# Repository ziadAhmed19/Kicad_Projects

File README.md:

## PCB Design Portfolio

This repository contains a collection of PCB design projects created using KiCad. Each project includes an interactive PCB viewer (iBOM), PCB images, and design files.

### Portfolio Website

https://ziadahmed19.github.io/Kicad_Projects/

### Featured Projects

- Tiny Boost Converter
- Breadboard Power Supply
- 2-Layer MCU Datalogger
- 4-Layer MCU Datalogger

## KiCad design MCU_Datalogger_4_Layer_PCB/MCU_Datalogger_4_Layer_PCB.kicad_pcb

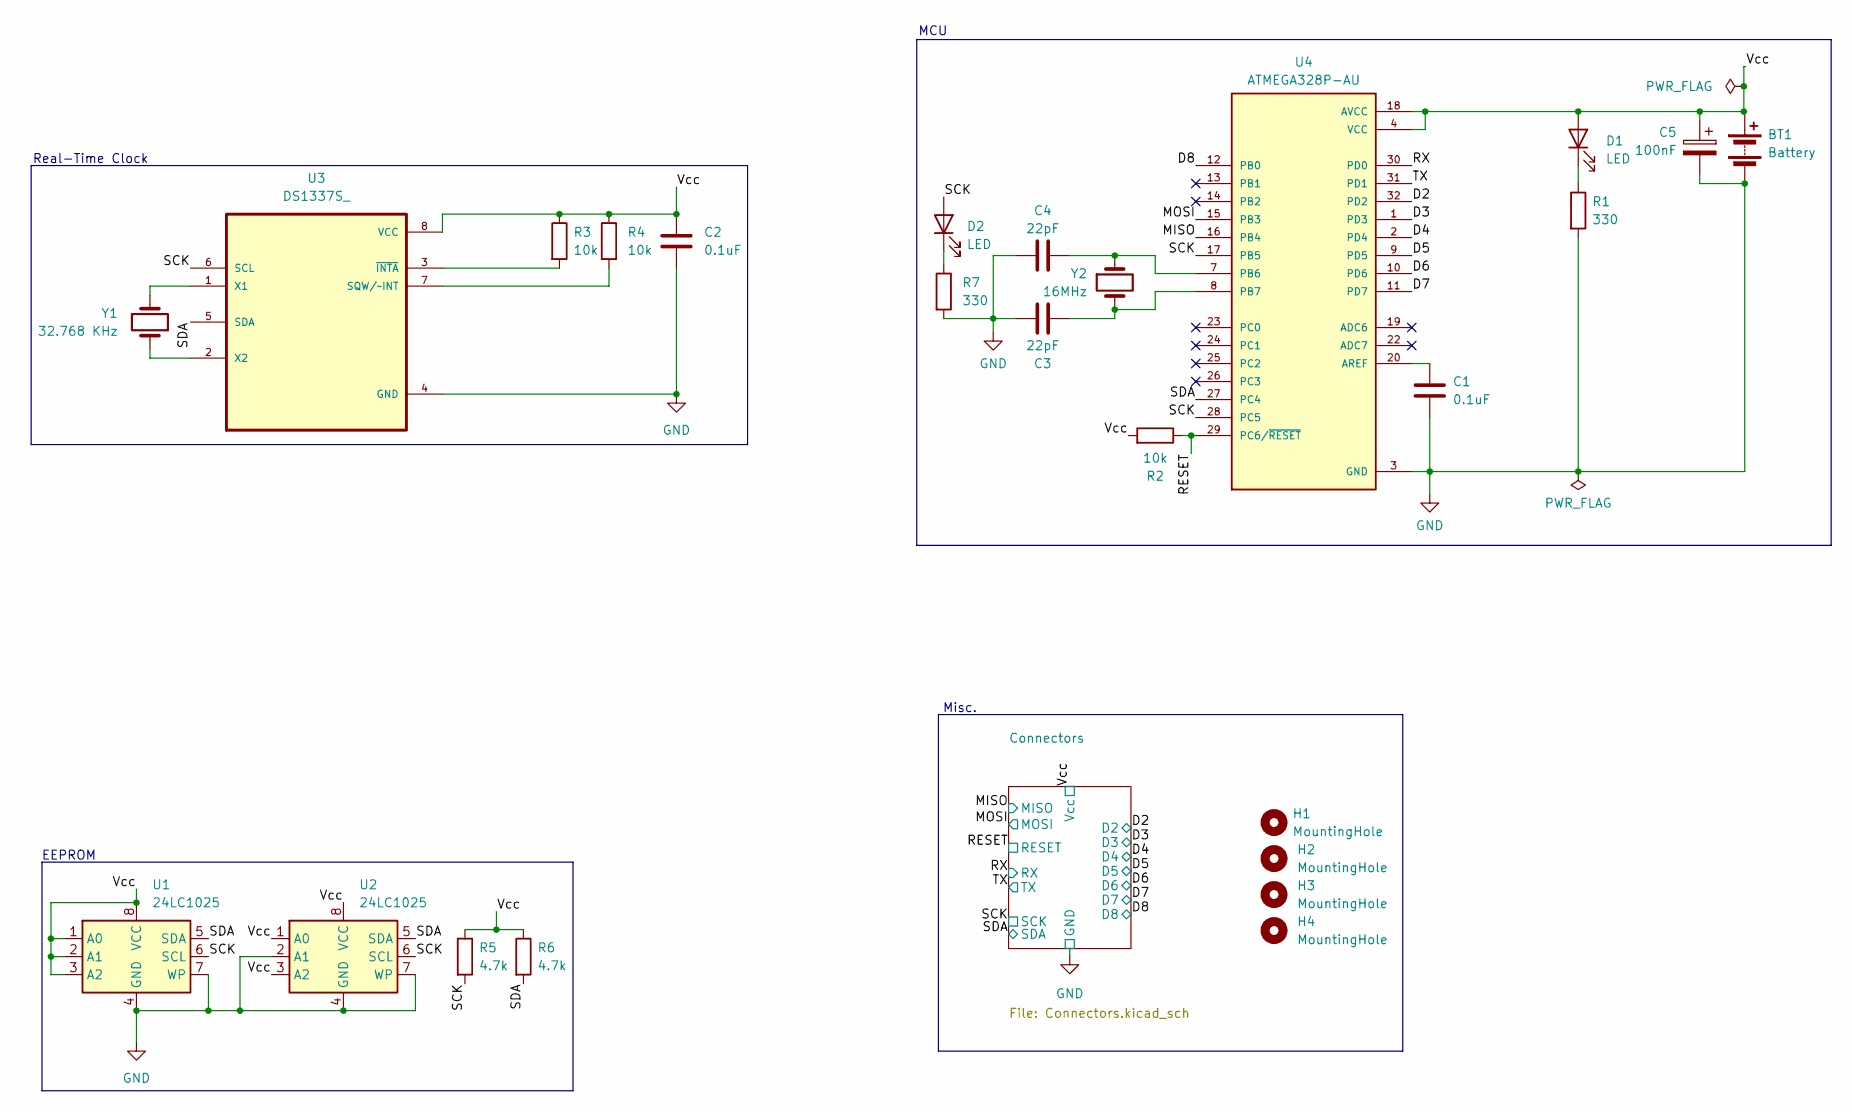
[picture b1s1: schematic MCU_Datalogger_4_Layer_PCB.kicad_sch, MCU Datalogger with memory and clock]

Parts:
BT1: Battery; PinHeader_1x02_P2.54mm_Vertical
C1, C2: 0.1uF; C_0805_2012Metric
C3, C4: 22pF; C_0805_2012Metric
C5: 100nF; C_0805_2012Metric
D1, D2: LED; LED_0805_2012Metric
H1, H2, H3, H4: MountingHole; MountingHole_2.1mm
R1, R7: 330; R_0805_2012Metric
R2, R3, R4: 10k; R_0805_2012Metric
R5, R6: 4.7k; R_0805_2012Metric
U1, U2: 24LC1025; SOIC-8_3.9x4.9mm_P1.27mm
U3: DS1337S_; SOIC127P600X175-8N
U4: ATMEGA328P-AU; QFP80P900X900X120-32N; PARTREV 8271A
Y1: 32.768 KHz; Crystal_SMD_5032-2Pin_5.0x3.2mm
Y2: 16MHz; Crystal_SMD_5032-2Pin_5.0x3.2mm

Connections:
/D2: U4.32 (PD2); also elsewhere on the board
/D3: U4.1 (PD3); also elsewhere on the board
/D4: U4.2 (PD4); also elsewhere on the board
/D5: U4.9 (PD5); also elsewhere on the board
/D6: U4.10 (PD6); also elsewhere on the board
/D7: U4.11 (PD7); also elsewhere on the board
/D8: U4.12 (PB0); also elsewhere on the board
/MISO: U4.16 (PB4); also elsewhere on the board
/MOSI: U4.15 (PB3); also elsewhere on the board
/RESET: R2.1, U4.29 (PC6/~RESET); also elsewhere on the board
/RX: U4.30 (PD0); also elsewhere on the board
/SCK: D2.2 (A), R5.2, U1.6 (SCL), U2.6 (SCL), U3.6 (SCL), U4.17 (PB5), U4.28 (PC5); also elsewhere on the board
/SDA: R6.2, U1.5 (SDA), U2.5 (SDA), U3.5 (SDA), U4.27 (PC4); also elsewhere on the board
/TX: U4.31 (PD1); also elsewhere on the board
GND: BT1.2 (-), C1.2, C2.2, C3.1, C4.2, C5.2, R1.2, R7.2, U1.4 (GND), U1.7 (WP), U2.2 (A1), U2.4 (GND), U2.7 (WP), U3.4 (GND), U4.3 (GND), U4.5 (GND), U4.21 (GND); also elsewhere on the board
unnamed: D1.1 (K), R1.1
unnamed: D2.1 (K), R7.1
unnamed: R4.2, U3.7 (SQW/~INT)
unnamed: U3.1 (X1), Y1.2
unnamed: U3.2 (X2), Y1.1
unnamed: R3.2, U3.3 (~INTA)
unnamed: C1.1, U4.20 (AREF)
unnamed: C4.1, U4.7 (PB6), Y2.1
unnamed: C3.2, U4.8 (PB7), Y2.2
VCC: BT1.1 (+), C2.1, C5.1, D1.2 (A), R2.2, R3.1, R4.1, R5.1, R6.1, U1.1 (A0), U1.2 (A1), U1.3 (A2), U1.8 (VCC), U2.1 (A0), U2.3 (A2), U2.8 (VCC), U3.8 (VCC), U4.4 (VCC), U4.6 (VCC), U4.18 (AVCC); also elsewhere on the board

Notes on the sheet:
MCU
EEPROM
Real-Time Clock
Misc.

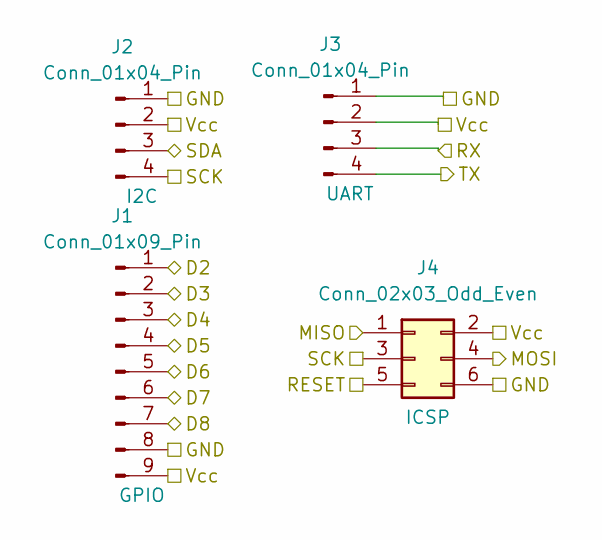
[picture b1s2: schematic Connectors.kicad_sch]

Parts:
J1: Conn_01x09_Pin; PinHeader_1x09_P2.54mm_Vertical
J2, J3: Conn_01x04_Pin; PinHeader_1x04_P2.54mm_Vertical
J4: Conn_02x03_Odd_Even; PinHeader_2x03_P2.54mm_Vertical

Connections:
/D2: J1.1; also elsewhere on the board
/D3: J1.2; also elsewhere on the board
/D4: J1.3; also elsewhere on the board
/D5: J1.4; also elsewhere on the board
/D6: J1.5; also elsewhere on the board
/D7: J1.6; also elsewhere on the board
/D8: J1.7; also elsewhere on the board
/MISO: J4.1; also elsewhere on the board
/MOSI: J4.4; also elsewhere on the board
/RESET: J4.5; also elsewhere on the board
/RX: J3.3; also elsewhere on the board
/SCK: J2.4, J4.3; also elsewhere on the board
/SDA: J2.3; also elsewhere on the board
/TX: J3.4; also elsewhere on the board
GND: J1.8, J2.1, J3.1, J4.6; also elsewhere on the board
VCC: J1.9, J2.2, J3.2, J4.2; also elsewhere on the board

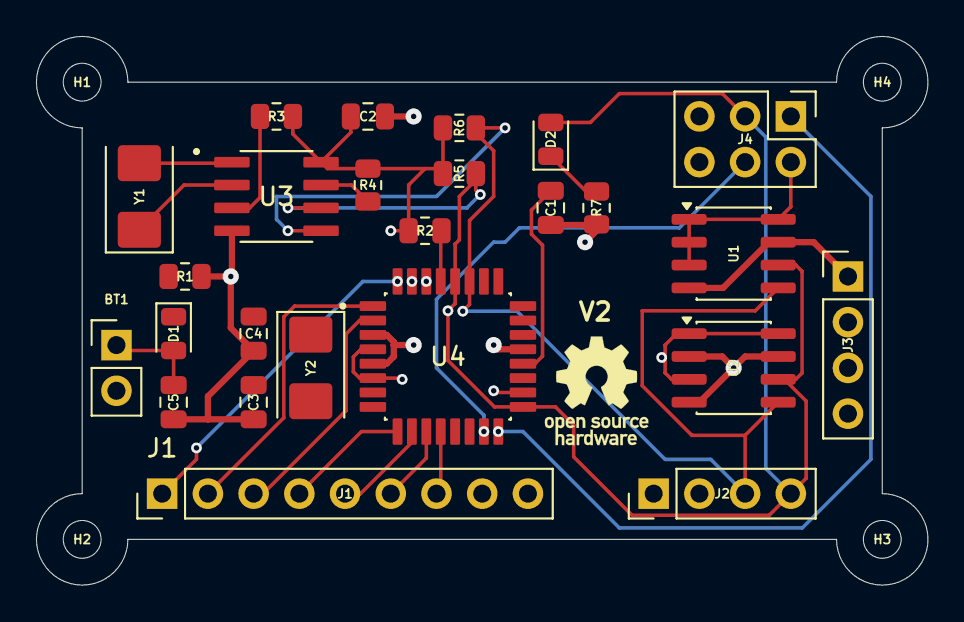
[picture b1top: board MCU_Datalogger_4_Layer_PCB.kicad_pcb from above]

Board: 4 copper layers, 49.5 x 30.5 mm, 29 parts (0 on the bottom side), 25 nets.

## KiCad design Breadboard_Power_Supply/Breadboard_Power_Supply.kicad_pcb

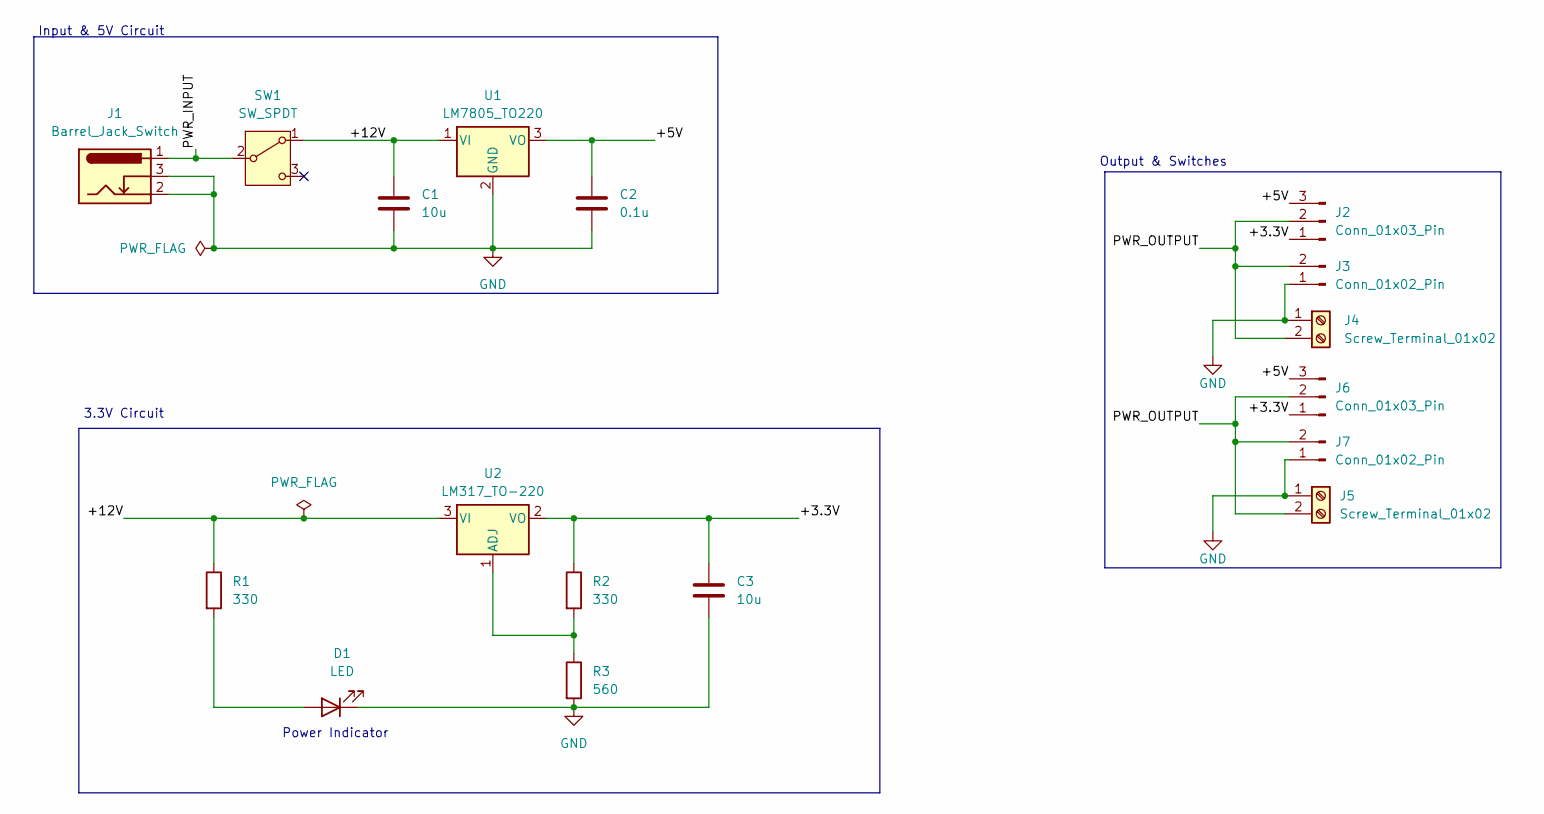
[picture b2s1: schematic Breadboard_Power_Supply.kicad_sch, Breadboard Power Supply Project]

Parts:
C1, C3: 10u; C_Disc_D3.0mm_W1.6mm_P2.50mm
C2: 0.1u; C_Disc_D3.0mm_W1.6mm_P2.50mm
D1: LED; LED_D5.0mm
J1: Barrel_Jack_Switch; BarrelJack_Horizontal
J2, J6: Conn_01x03_Pin; PinHeader_1x03_P2.54mm_Vertical
J3, J7: Conn_01x02_Pin; PinHeader_1x02_P2.54mm_Vertical
J4, J5: Screw_Terminal_01x02; TerminalBlock_MaiXu_MX126-5.0-02P_1x02_P5.00mm
R1, R2: 330; R_Axial_DIN0207_L6.3mm_D2.5mm_P7.62mm_Horizontal
R3: 560; R_Axial_DIN0207_L6.3mm_D2.5mm_P7.62mm_Horizontal
SW1: SW_SPDT; SW_Slide-03_Wuerth-WS-SLTV_10x2.5x6.4_P2.54mm
U1: LM7805_TO220; TO-220-3_Vertical
U2: LM317_TO-220; TO-220-3_Vertical

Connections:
/+3.3V: C3.1, J2.1, J6.1, R2.1, U2.2 (VO)
/+5V: C2.1, J2.3, J6.3, U1.3 (VO)
/+12V: C1.1, R1.1, SW1.1 (A), U1.1 (VI), U2.3 (VI)
/PWR_INPUT: J1.1, SW1.2 (B)
/PWR_OUTPUT: J2.2, J3.2, J4.2, J5.2, J6.2, J7.2
GND: C1.2, C2.2, C3.2, D1.1 (K), J1.2, J1.3, J3.1, J4.1, J5.1, J7.1, R3.2, U1.2 (GND)
unnamed: D1.2 (A), R1.2
unnamed: R2.2, R3.1, U2.1 (ADJ)

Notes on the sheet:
3.3V Circuit
Power Indicator
Output & Switches
Input & 5V Circuit

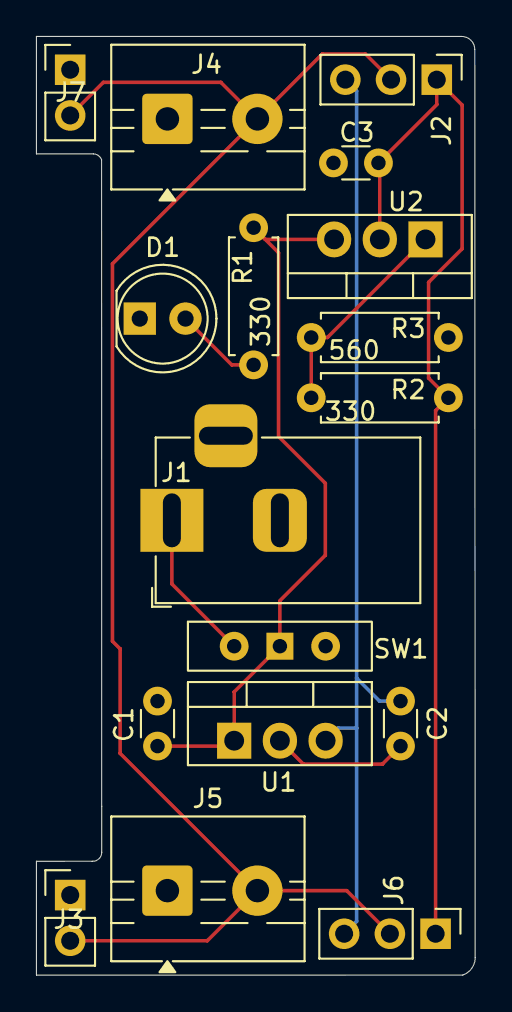
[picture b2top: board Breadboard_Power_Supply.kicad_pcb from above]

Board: 2 copper layers, 24.4 x 52.1 mm, 17 parts (0 on the bottom side), 8 nets.

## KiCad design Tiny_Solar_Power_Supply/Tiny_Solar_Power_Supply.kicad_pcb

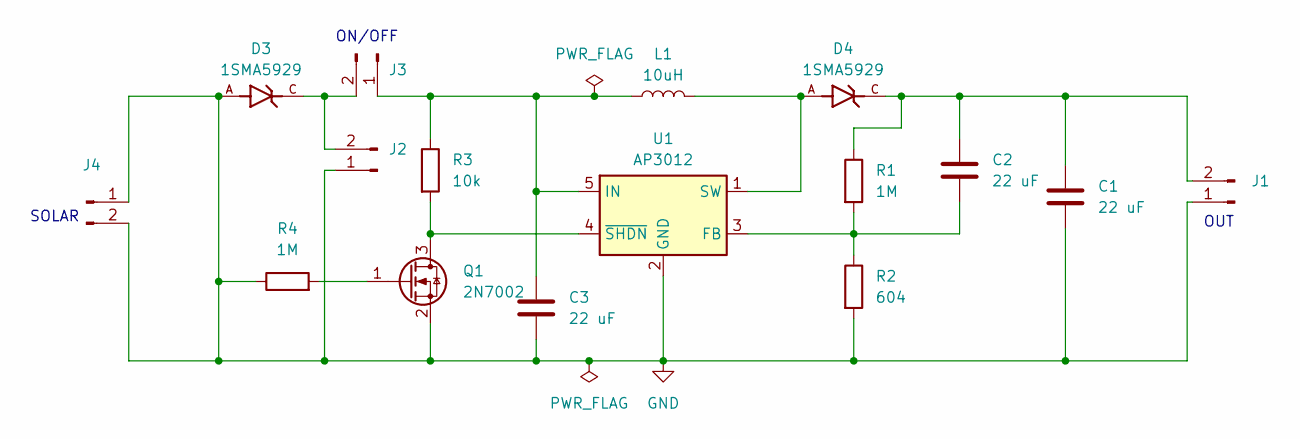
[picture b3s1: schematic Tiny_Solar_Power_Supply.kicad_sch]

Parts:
C1: 22 uF; C_0805_2012Metric
C2, C3: 22 uF; C_1206_3216Metric
D3, D4: 1SMA5929; DIOM4325X250N; PARTREV B2102; DigiKey_Part_Number 1801-1SMA5929CT-ND
J1, J2, J3: Conn_01x02_Pin; PinHeader_1x02_P2.00mm_Vertical
J4: Conn_01x02_Pin; TE_440055-2_1x02_P2.00mm_Horizontal
L1: 10uH; L_1210_3225Metric
Q1: 2N7002; SOT-23
R1, R4: 1M; R_0805_2012Metric
R2: 604; R_0805_2012Metric
R3: 10k; R_0805_2012Metric
U1: AP3012; SOT-23-5

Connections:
GND: C1.2, C3.2, D3.A, J1.1, J2.1, J4.1, J4.2, Q1.2 (S), R2.2, R4.1, U1.2 (GND)
unnamed: C1.1, C2.1, D4.C, J1.2, R1.1
unnamed: D3.C, J2.2, J3.2
unnamed: C3.1, J3.1, L1.1, R3.1, U1.5 (IN)
unnamed: Q1.3 (D), R3.2, U1.4 (~SHDN)
unnamed: Q1.1 (G), R4.2
unnamed: C2.2, R1.2, R2.1, U1.3 (FB)
unnamed: D4.A, L1.2, U1.1 (SW)

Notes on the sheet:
OUT
ON/OFF
SOLAR

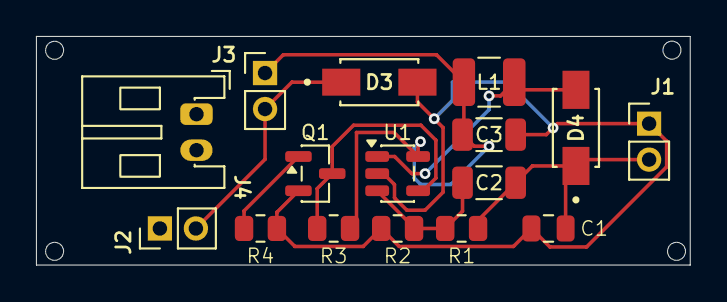
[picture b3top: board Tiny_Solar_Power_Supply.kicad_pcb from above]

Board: 2 copper layers, 36.3 x 12.7 mm, 16 parts (0 on the bottom side), 8 nets.

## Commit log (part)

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2026-06-23 init commit
2026-06-24 Improved PCB Layout
2026-06-24 Completed BreadBoard Power Supply Project
